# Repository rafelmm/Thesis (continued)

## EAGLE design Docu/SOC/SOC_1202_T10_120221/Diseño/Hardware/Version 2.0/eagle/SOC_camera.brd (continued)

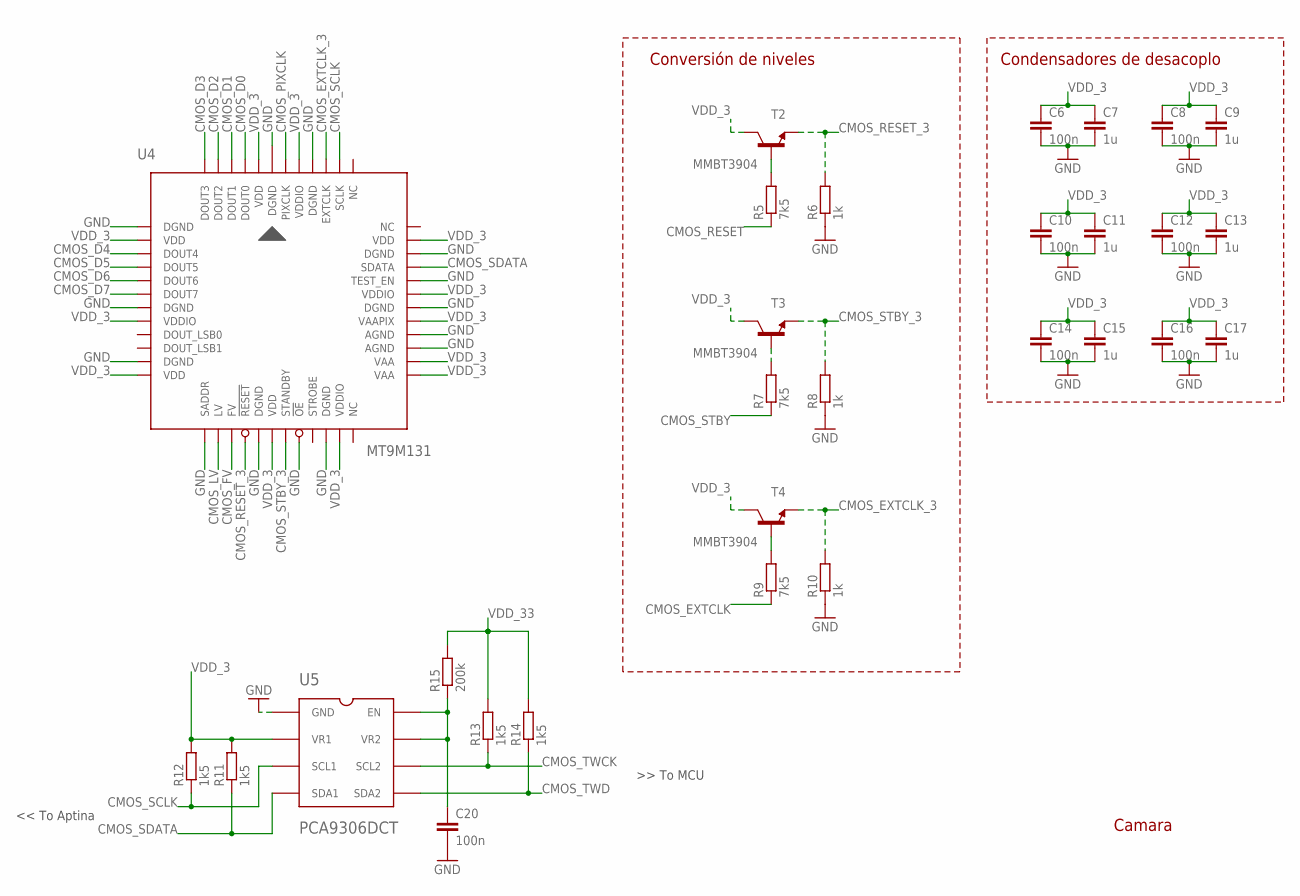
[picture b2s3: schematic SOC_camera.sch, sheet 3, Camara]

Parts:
C6, C8, C10, C12, C14, C16, C20: 100n; C0402
C7, C9, C11, C13, C15, C17: 1u; C0402
R5, R7, R9: 7k5; R0603
R6, R8, R10: 1k; R0603
R11, R12, R13, R14: 1k5; R0402
R15: 200k; R0402
T2, T3, T4: MMBT3904; SOT23-BEC
U4: MT9M131; APTINA
U5: PCA9306DCT; SSOP8; MPN PCA9306DCTR

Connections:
CMOS_D0: U4.3 (DOUT0); also elsewhere on the board
CMOS_D1: U4.4 (DOUT1); also elsewhere on the board
CMOS_D2: U4.5 (DOUT2); also elsewhere on the board
CMOS_D3: U4.6 (DOUT3); also elsewhere on the board
CMOS_D4: U4.9 (DOUT4); also elsewhere on the board
CMOS_D5: U4.10 (DOUT5); also elsewhere on the board
CMOS_D6: U4.11 (DOUT6); also elsewhere on the board
CMOS_D7: U4.12 (DOUT7); also elsewhere on the board
CMOS_EXTCLK: R9.1; also elsewhere on the board
CMOS_EXTCLK_3: R10.2, T4.E, U4.45 (EXTCLK)
CMOS_FV: U4.21 (FV); also elsewhere on the board
CMOS_LV: U4.20 (LV); also elsewhere on the board
CMOS_PIXCLK: U4.48 (PIXCLK); also elsewhere on the board
CMOS_RESET: R5.1; also elsewhere on the board
CMOS_RESET_3: R6.2, T2.E, U4.22 (!RESET)
CMOS_SCLK: R12.1, U4.44 (SCLK), U5.3 (SCL1)
CMOS_SDATA: R11.1, U4.39 (SDATA), U5.4 (SDA1)
CMOS_STBY: R7.1; also elsewhere on the board
CMOS_STBY_3: R8.2, T3.E, U4.25 (STANDBY)
CMOS_TWCK: R13.1, U5.6 (SCL2); also elsewhere on the board
CMOS_TWD: R14.1, U5.5 (SDA2); also elsewhere on the board
GND: C6.2, C7.2, C8.2, C9.2, C10.2, C11.2, C12.2, C13.2, C14.2, C15.2, C16.2, C17.2, C20.2, R6.1, R8.1, R10.1, U4.1 (DGND), U4.7 (DGND), U4.13 (DGND), U4.17 (DGND), U4.19 (SADDR), U4.23 (DGND), U4.26 (!OE), U4.28 (DGND), U4.33 (AGND), U4.34 (AGND), U4.36 (DGND), U4.38 (TEST_EN), U4.40 (DGND), U4.46 (DGND), U5.1 (GND); also elsewhere on the board
unnamed: R7.2, T3.B
unnamed: R9.2, T4.B
unnamed: R5.2, T2.B
unnamed: C20.1, R15.1, U5.7 (VR2), U5.8 (EN)
VDD_3: C6.1, C7.1, C8.1, C9.1, C10.1, C11.1, C12.1, C13.1, C14.1, C15.1, C16.1, C17.1, R11.2, R12.2, T2.C, T3.C, T4.C, U4.2 (VDD), U4.8 (VDD), U4.14 (VDDIO), U4.18 (VDD), U4.24 (VDD), U4.29 (VDDIO), U4.31 (VAA), U4.32 (VAA), U4.35 (VAAPIX), U4.37 (VDDIO), U4.41 (VDD), U4.47 (VDDIO), U5.2 (VR1); also elsewhere on the board
VDD_33: R13.2, R14.2, R15.2; also elsewhere on the board

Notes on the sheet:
Camara
Condensadores de desacoplo
Conversión de niveles
<< To Aptina

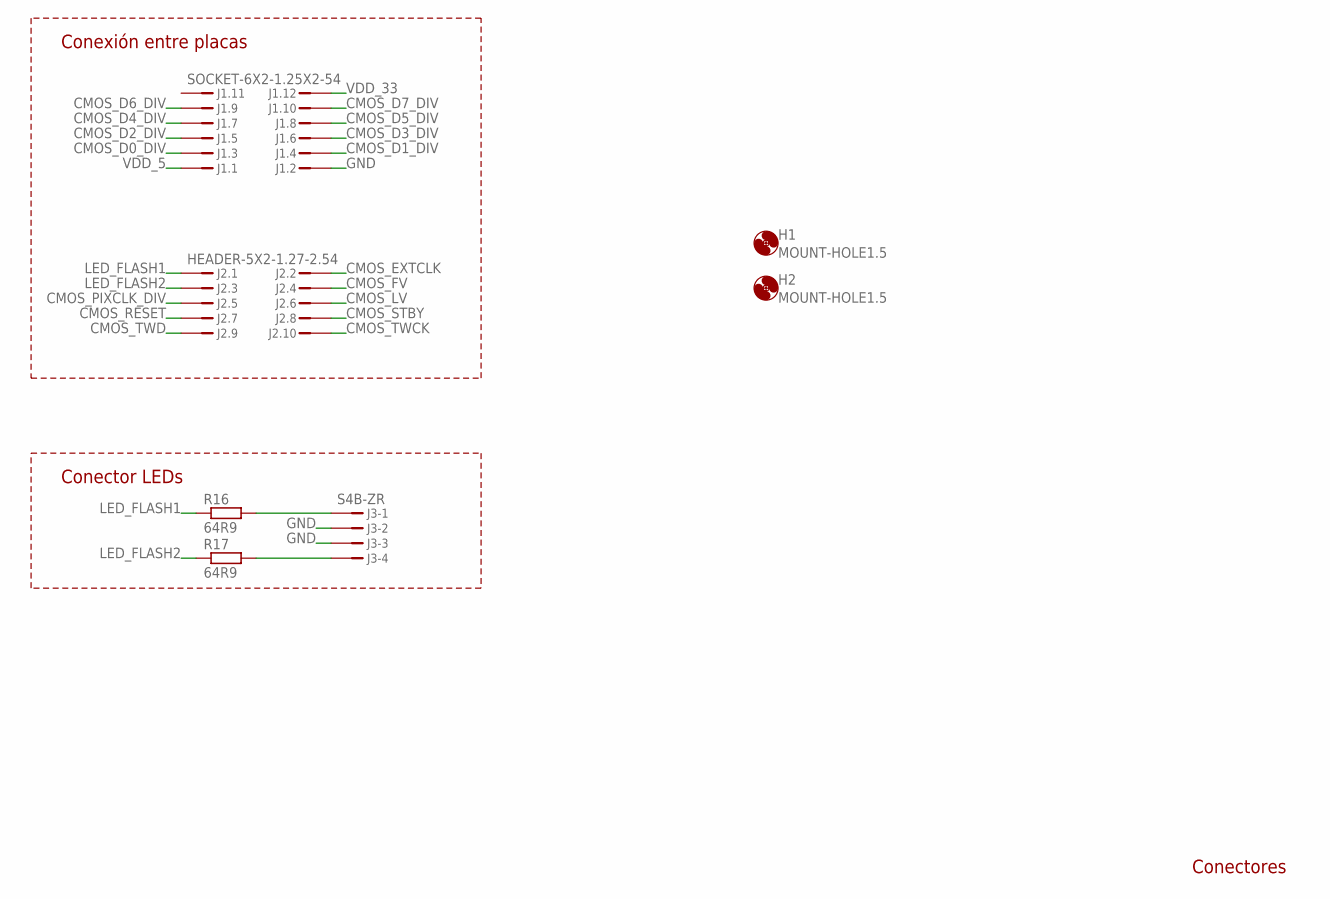
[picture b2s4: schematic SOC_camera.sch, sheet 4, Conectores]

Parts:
H1, H2: MOUNT-HOLE1.5; 1,5
J1: SOCKET-6X2-1.25X2-54; SOCKET-THD-6X2(1.27X2.54)
J2: HEADER-5X2-1.27-2.54; HEADER-THD-5X2(1.27X2.54)
J3: S4B-ZR
R16, R17: 64R9; R0603

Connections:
CMOS_D0_DIV: J1.P3; also elsewhere on the board
CMOS_D1_DIV: J1.P4; also elsewhere on the board
CMOS_D2_DIV: J1.P5; also elsewhere on the board
CMOS_D3_DIV: J1.P6; also elsewhere on the board
CMOS_D4_DIV: J1.P7; also elsewhere on the board
CMOS_D5_DIV: J1.P8; also elsewhere on the board
CMOS_D6_DIV: J1.P9; also elsewhere on the board
CMOS_D7_DIV: J1.P10; also elsewhere on the board
CMOS_EXTCLK: J2.2; also elsewhere on the board
CMOS_FV: J2.4; also elsewhere on the board
CMOS_LV: J2.6; also elsewhere on the board
CMOS_PIXCLK_DIV: J2.5; also elsewhere on the board
CMOS_RESET: J2.7; also elsewhere on the board
CMOS_STBY: J2.8; also elsewhere on the board
CMOS_TWCK: J2.10; also elsewhere on the board
CMOS_TWD: J2.9; also elsewhere on the board
GND: J1.P2, J3.2, J3.3; also elsewhere on the board
LED_FLASH1: J2.1, R16.1
LED_FLASH2: J2.3, R17.1
unnamed: J3.4, R17.2
unnamed: J3.1, R16.2
VDD_5: J1.P1; also elsewhere on the board
VDD_33: J1.P12; also elsewhere on the board

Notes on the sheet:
Conectores
Conexión entre placas
Conector LEDs

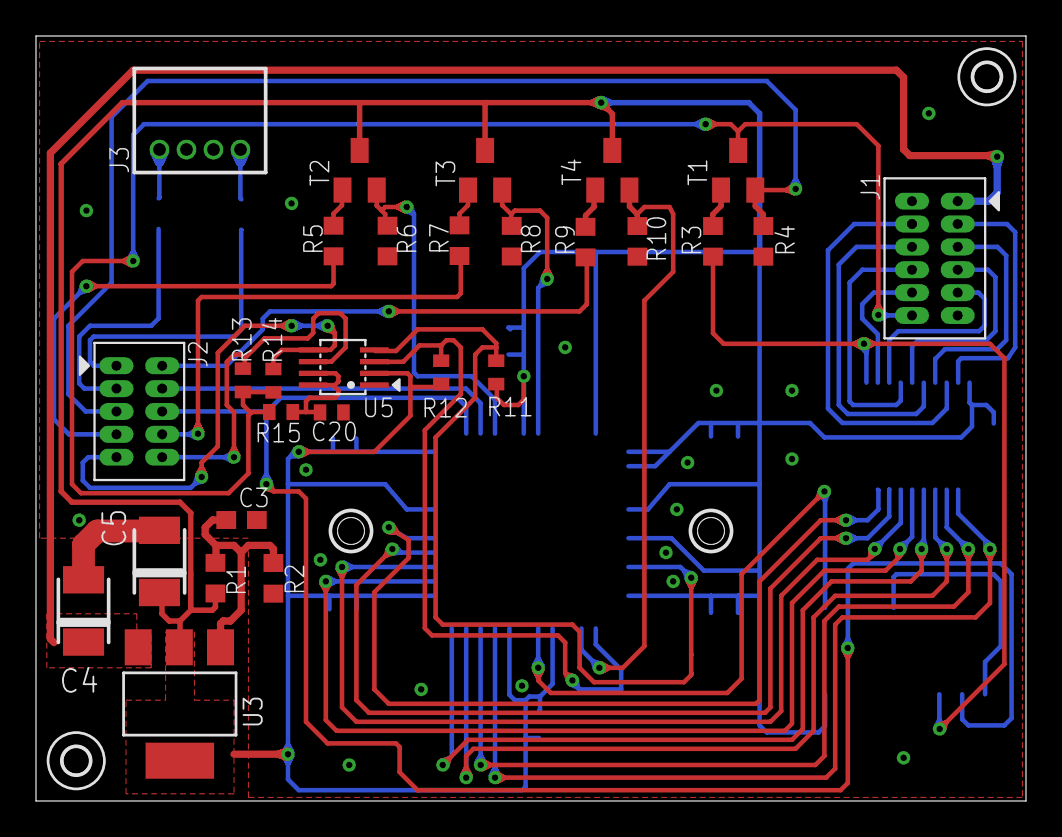
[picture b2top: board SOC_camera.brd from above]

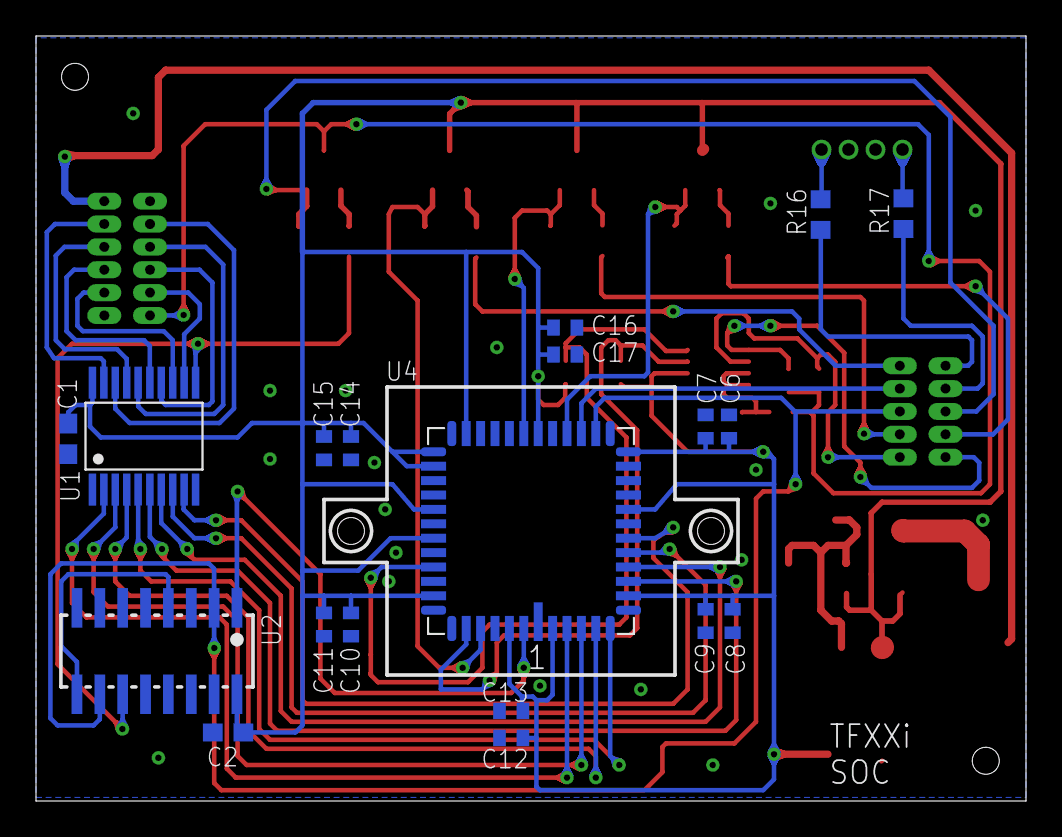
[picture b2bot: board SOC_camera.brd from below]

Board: 2 copper layers, 55.0 x 42.5 mm, 49 parts (19 on the bottom side), 46 nets.

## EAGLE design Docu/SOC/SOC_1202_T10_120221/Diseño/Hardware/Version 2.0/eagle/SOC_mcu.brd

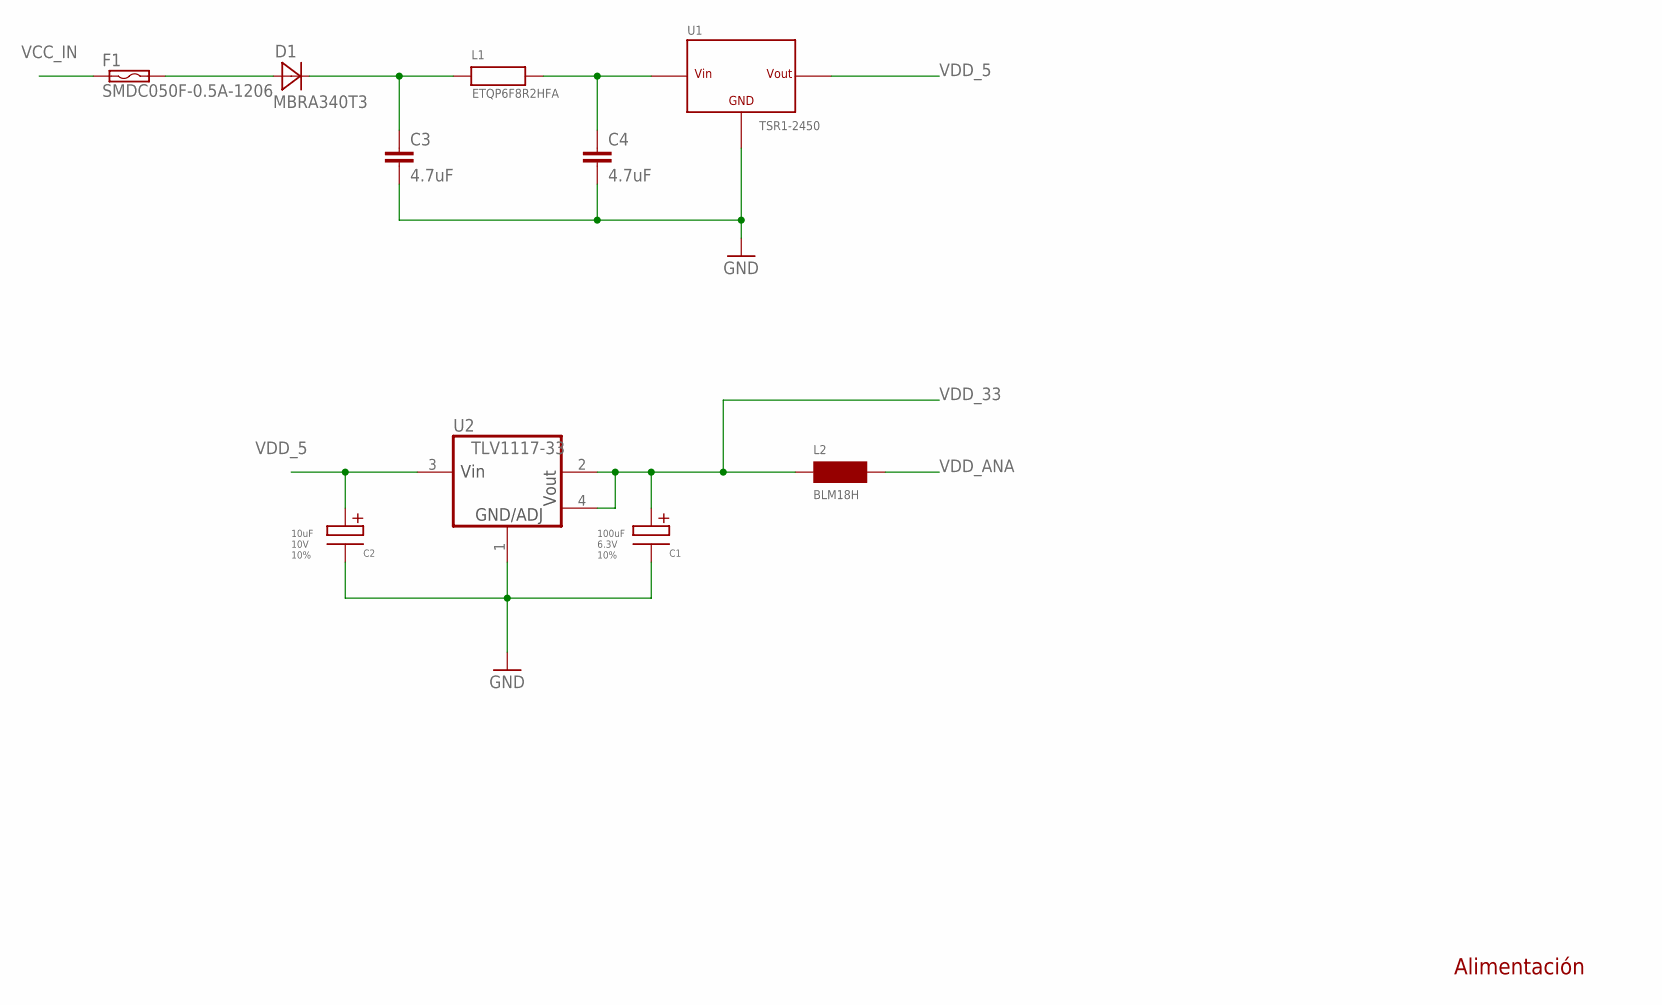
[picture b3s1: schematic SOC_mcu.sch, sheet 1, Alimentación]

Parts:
C1: 100uF; 3528-21
C2: 10uF; 3528-21
C3, C4: 4.7uF; C0805
D1: MBRA340T3; SMA
F1: SMDC050F-0.5A-1206; 1206
L1: ETQP6F8R2HFA; PAN_COIL_CHOKE
L2: BLM18H; 0603
U1: TSR1-2450; TO220V
U2: TLV1117-33; SOT223; MPN TLV1117-CDCY

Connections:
GND: C1.NEG, C2.NEG, C3.2, C4.2, U1.2 (GND), U2.1 (GND); also elsewhere on the board
unnamed: C4.1, L1.2, U1.1 (+VIN)
unnamed: C3.1, D1.C, L1.1
unnamed: D1.A, F1.2
VCC_IN: F1.1; also elsewhere on the board
VDD_5: C2.POS, U1.3 (VOUT), U2.3 (VIN); also elsewhere on the board
VDD_33: C1.POS, L2.1, U2.2 (VOUT), U2.4 (VO2); also elsewhere on the board
VDD_ANA: L2.2; also elsewhere on the board

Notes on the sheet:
Alimentación

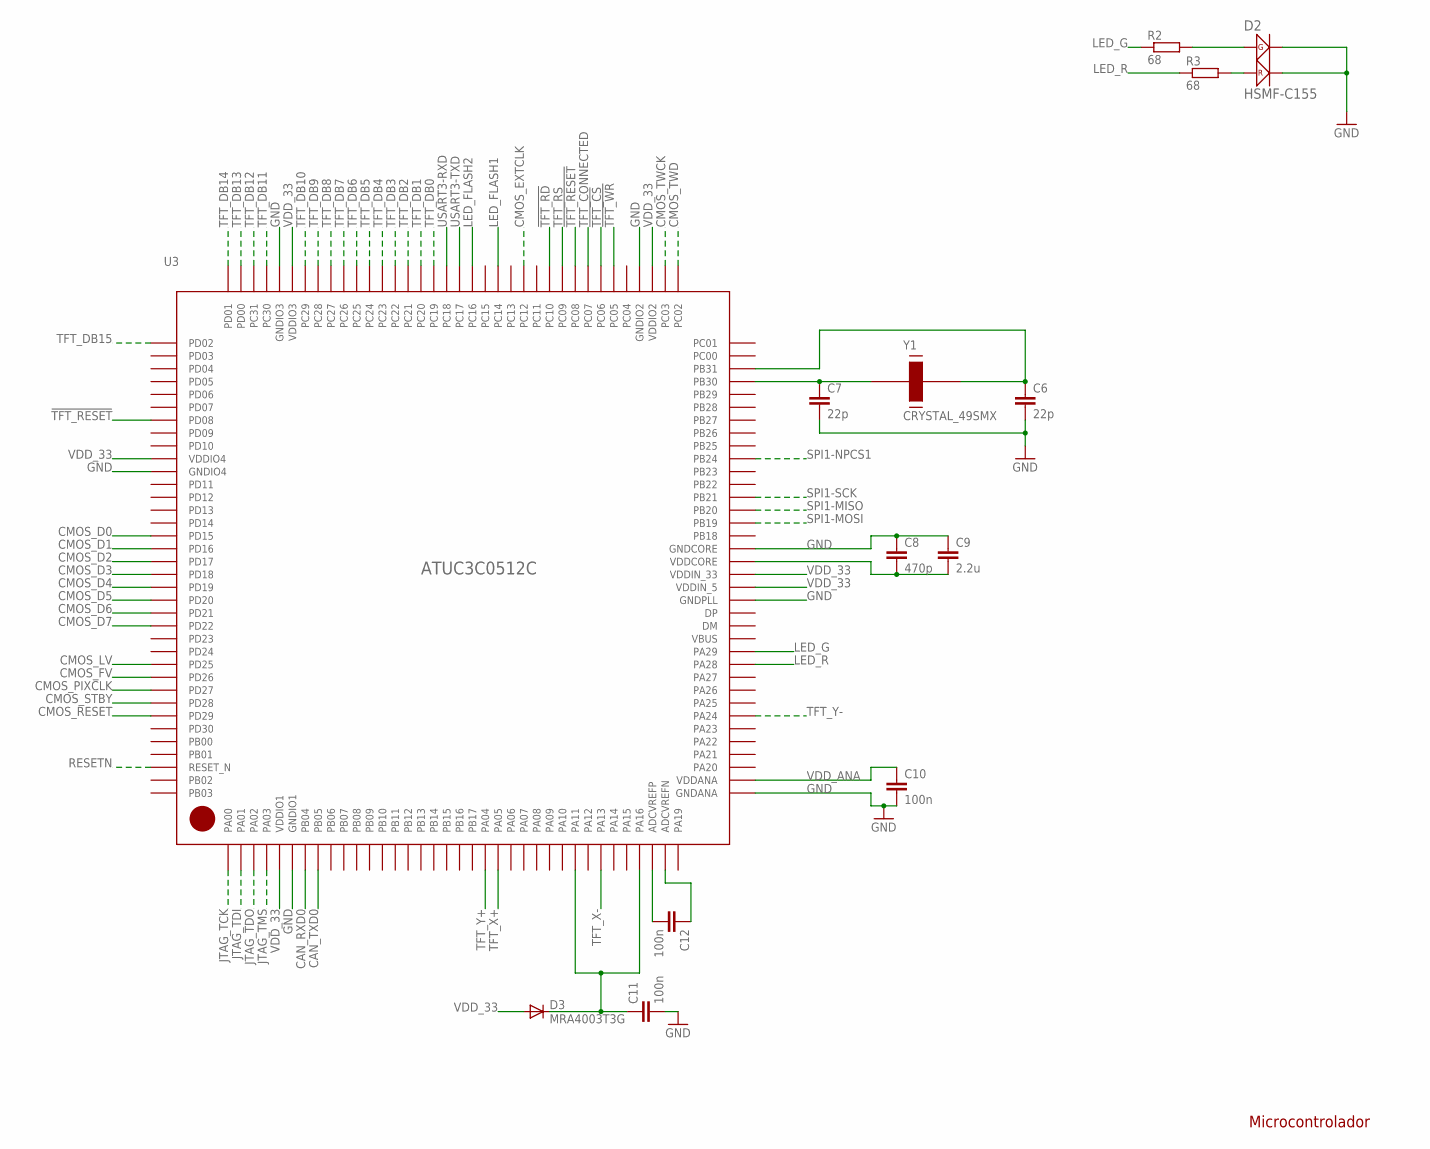
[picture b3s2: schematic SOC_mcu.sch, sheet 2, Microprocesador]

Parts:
C6, C7: 22p; C0603
C8: 470p; C0603
C9: 2.2u; C0603
C10, C11, C12: 100n; C0603
D2: HSMF-C155; HSMF-C
D3: MRA4003T3G; DO214AC
R2, R3: 68; R0603
U3: ATUC3C0512C; TQFP144
Y1: CRYSTAL_49SMX; HC49UP

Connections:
!TFT_CS: U3.79 (PC06); also elsewhere on the board
!TFT_RD: U3.83 (PC10); also elsewhere on the board
!TFT_RESET: U3.81 (PC08), U3.115 (PD08); also elsewhere on the board
!TFT_WR: U3.78 (PC05); also elsewhere on the board
CAN_RXD0: U3.7 (PB04); also elsewhere on the board
CAN_TXD0: U3.8 (PB05); also elsewhere on the board
CMOS_D0: U3.124 (PD15); also elsewhere on the board
CMOS_D1: U3.125 (PD16); also elsewhere on the board
CMOS_D2: U3.126 (PD17); also elsewhere on the board
CMOS_D3: U3.127 (PD18); also elsewhere on the board
CMOS_D4: U3.128 (PD19); also elsewhere on the board
CMOS_D5: U3.129 (PD20); also elsewhere on the board
CMOS_D6: U3.130 (PD21); also elsewhere on the board
CMOS_D7: U3.131 (PD22); also elsewhere on the board
CMOS_EXTCLK: U3.85 (PC12); also elsewhere on the board
CMOS_FV: U3.135 (PD26); also elsewhere on the board
CMOS_LV: U3.134 (PD25); also elsewhere on the board
CMOS_PIXCLK: U3.136 (PD27); also elsewhere on the board
CMOS_RESET: U3.138 (PD29); also elsewhere on the board
CMOS_STBY: U3.137 (PD28); also elsewhere on the board
CMOS_TWCK: U3.74 (PC03); also elsewhere on the board
CMOS_TWD: U3.73 (PC02); also elsewhere on the board
GND: C6.2, C7.2, C8.1, C9.1, C10.2, C11.2, D2.2, D2.4, U3.6 (GNDIO1), U3.37 (GNDANA), U3.52 (GNDPLL), U3.56 (GNDCORE), U3.76 (GNDIO2), U3.104 (GNDIO3), U3.119 (GNDIO4); also elsewhere on the board
JTAG_TCK: U3.1 (PA00); also elsewhere on the board
JTAG_TDI: U3.2 (PA01); also elsewhere on the board
JTAG_TDO: U3.3 (PA02); also elsewhere on the board
JTAG_TMS: U3.4 (PA03); also elsewhere on the board
LED_FLASH1: U3.87 (PC14); also elsewhere on the board
LED_FLASH2: U3.89 (PC16); also elsewhere on the board
LED_G: R2.1, U3.48 (PA29)
LED_R: R3.1, U3.47 (PA28)
unnamed: C6.1, U3.70 (PB31), Y1.2
unnamed: C7.1, U3.69 (PB30), Y1.1
unnamed: C8.2, C9.2, U3.55 (VDDCORE)
unnamed: D2.1, R2.2
unnamed: D2.3, R3.2
unnamed: C11.1, D3.C, U3.28 (PA11), U3.33 (PA16)
unnamed: C12.2, U3.34 (ADCVREFP)
unnamed: C12.1, U3.35 (ADCVREFN)
RESETN: U3.142 (RESET_N); also elsewhere on the board
SPI1-MISO: U3.59 (PB20); also elsewhere on the board
SPI1-MOSI: U3.58 (PB19); also elsewhere on the board
SPI1-NPCS1: U3.63 (PB24); also elsewhere on the board
SPI1-SCK: U3.60 (PB21); also elsewhere on the board
TFT_CONNECTED: U3.80 (PC07); also elsewhere on the board
TFT_DB0: U3.92 (PC19); also elsewhere on the board
TFT_DB1: U3.93 (PC20); also elsewhere on the board
TFT_DB2: U3.94 (PC21); also elsewhere on the board
TFT_DB3: U3.95 (PC22); also elsewhere on the board
TFT_DB4: U3.96 (PC23); also elsewhere on the board
TFT_DB5: U3.97 (PC24); also elsewhere on the board
TFT_DB6: U3.98 (PC25); also elsewhere on the board
TFT_DB7: U3.99 (PC26); also elsewhere on the board
TFT_DB8: U3.100 (PC27); also elsewhere on the board
TFT_DB9: U3.101 (PC28); also elsewhere on the board
TFT_DB10: U3.102 (PC29); also elsewhere on the board
TFT_DB11: U3.105 (PC30); also elsewhere on the board
TFT_DB12: U3.106 (PC31); also elsewhere on the board
TFT_DB13: U3.107 (PD00); also elsewhere on the board
TFT_DB14: U3.108 (PD01); also elsewhere on the board
TFT_DB15: U3.109 (PD02); also elsewhere on the board
TFT_RS: U3.82 (PC09); also elsewhere on the board
TFT_X+: U3.22 (PA05); also elsewhere on the board
TFT_X-: U3.30 (PA13); also elsewhere on the board
TFT_Y+: U3.21 (PA04); also elsewhere on the board
TFT_Y-: U3.43 (PA24); also elsewhere on the board
USART3-RXD: U3.91 (PC18); also elsewhere on the board
USART3-TXD: U3.90 (PC17); also elsewhere on the board
VDD_33: D3.A, U3.5 (VDDIO1), U3.53 (VDDIN_5), U3.54 (VDDIN_33), U3.75 (VDDIO2), U3.103 (VDDIO3), U3.118 (VDDIO4); also elsewhere on the board
VDD_ANA: C10.1, U3.38 (VDDANA); also elsewhere on the board

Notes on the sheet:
Microcontrolador

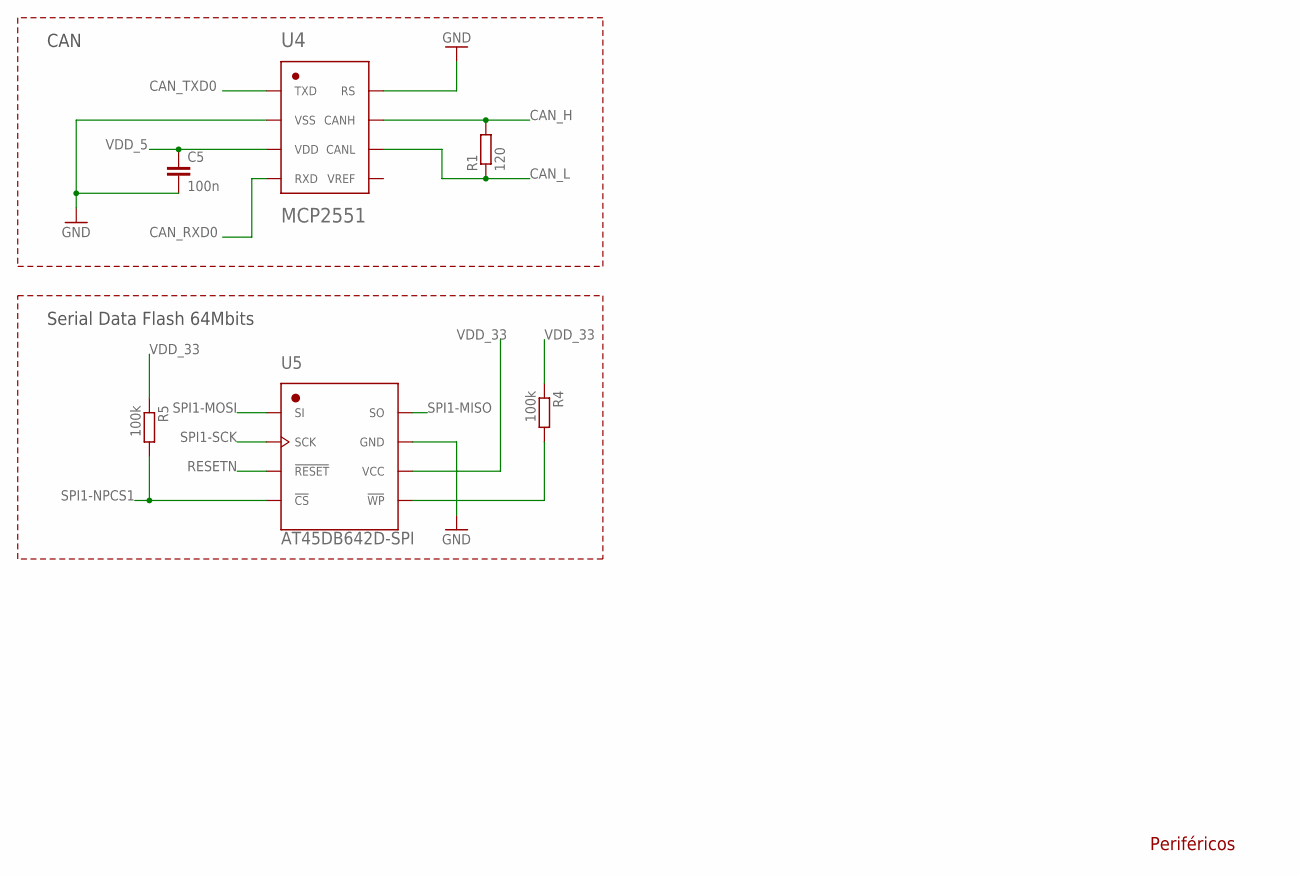
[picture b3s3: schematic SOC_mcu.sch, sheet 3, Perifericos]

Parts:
C5: 100n; C0603
R1: 120; R0805
R4, R5: 100k; R0603
U4: MCP2551; SO08
U5: AT45DB642D-SPI; 8CN3

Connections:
CAN_H: R1.2, U4.7 (CANH); also elsewhere on the board
CAN_L: R1.1, U4.6 (CANL); also elsewhere on the board
CAN_RXD0: U4.4 (RXD); also elsewhere on the board
CAN_TXD0: U4.1 (TXD); also elsewhere on the board
GND: C5.2, U4.2 (VSS), U4.8 (RS), U5.7 (GND); also elsewhere on the board
unnamed: R4.2, U5.5 (!WP)
RESETN: U5.3 (!RESET); also elsewhere on the board
SPI1-MISO: U5.8 (SO); also elsewhere on the board
SPI1-MOSI: U5.1 (SI); also elsewhere on the board
SPI1-NPCS1: R5.2, U5.4 (!CS); also elsewhere on the board
SPI1-SCK: U5.2 (SCK); also elsewhere on the board
VDD_5: C5.1, U4.3 (VDD); also elsewhere on the board
VDD_33: R4.1, R5.1, U5.6 (VCC); also elsewhere on the board

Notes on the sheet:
CAN
Serial Data Flash 64Mbits
Periféricos

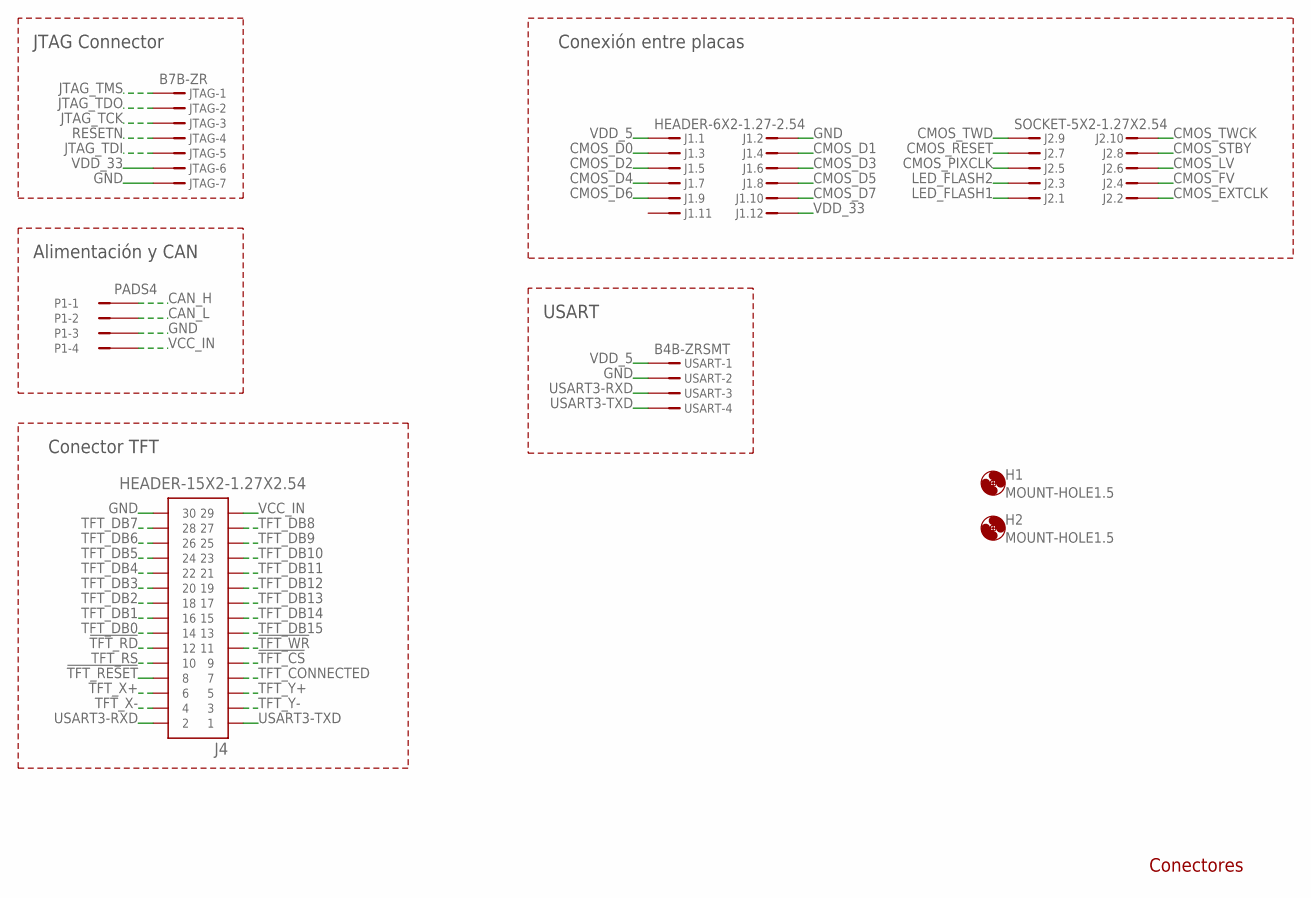
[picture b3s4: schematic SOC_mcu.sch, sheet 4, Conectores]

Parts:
H1, H2: MOUNT-HOLE1.5; 1,5
J1: HEADER-6X2-1.27-2.54; HEADER-THD-6X2(1.27X2.54)
J2: SOCKET-5X2-1.27X2.54; SOCKET-THD-5X2(1.27X2.54)
J4: HEADER-15X2-1.27X2.54; HEADER-THD-15X2(1.27X2.54)
JTAG: B7B-ZR
P1: PADS4; CAN+POWER
USART: B4B-ZRSMT; SM4-TF

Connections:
!TFT_CS: J4.9; also elsewhere on the board
!TFT_RD: J4.12; also elsewhere on the board
!TFT_RESET: J4.8; also elsewhere on the board
!TFT_WR: J4.11; also elsewhere on the board
CAN_H: P1.1; also elsewhere on the board
CAN_L: P1.2; also elsewhere on the board
CMOS_D0: J1.3; also elsewhere on the board
CMOS_D1: J1.4; also elsewhere on the board
CMOS_D2: J1.5; also elsewhere on the board
CMOS_D3: J1.6; also elsewhere on the board
CMOS_D4: J1.7; also elsewhere on the board
CMOS_D5: J1.8; also elsewhere on the board
CMOS_D6: J1.9; also elsewhere on the board
CMOS_D7: J1.10; also elsewhere on the board
CMOS_EXTCLK: J2.P2; also elsewhere on the board
CMOS_FV: J2.P4; also elsewhere on the board
CMOS_LV: J2.P6; also elsewhere on the board
CMOS_PIXCLK: J2.P5; also elsewhere on the board
CMOS_RESET: J2.P7; also elsewhere on the board
CMOS_STBY: J2.P8; also elsewhere on the board
CMOS_TWCK: J2.P10; also elsewhere on the board
CMOS_TWD: J2.P9; also elsewhere on the board
GND: J1.2, J4.30, JTAG.7, P1.3, USART.2; also elsewhere on the board
JTAG_TCK: JTAG.3; also elsewhere on the board
JTAG_TDI: JTAG.5; also elsewhere on the board
JTAG_TDO: JTAG.2; also elsewhere on the board
JTAG_TMS: JTAG.1; also elsewhere on the board
LED_FLASH1: J2.P1; also elsewhere on the board
LED_FLASH2: J2.P3; also elsewhere on the board
RESETN: JTAG.4; also elsewhere on the board
TFT_CONNECTED: J4.7; also elsewhere on the board
TFT_DB0: J4.14; also elsewhere on the board
TFT_DB1: J4.16; also elsewhere on the board
TFT_DB2: J4.18; also elsewhere on the board
TFT_DB3: J4.20; also elsewhere on the board
TFT_DB4: J4.22; also elsewhere on the board
TFT_DB5: J4.24; also elsewhere on the board
TFT_DB6: J4.26; also elsewhere on the board
TFT_DB7: J4.28; also elsewhere on the board
TFT_DB8: J4.27; also elsewhere on the board
TFT_DB9: J4.25; also elsewhere on the board
TFT_DB10: J4.23; also elsewhere on the board
TFT_DB11: J4.21; also elsewhere on the board
TFT_DB12: J4.19; also elsewhere on the board
TFT_DB13: J4.17; also elsewhere on the board
TFT_DB14: J4.15; also elsewhere on the board
TFT_DB15: J4.13; also elsewhere on the board
TFT_RS: J4.10; also elsewhere on the board
TFT_X+: J4.6; also elsewhere on the board
TFT_X-: J4.4; also elsewhere on the board
TFT_Y+: J4.5; also elsewhere on the board
TFT_Y-: J4.3; also elsewhere on the board
USART3-RXD: J4.2, USART.3; also elsewhere on the board
USART3-TXD: J4.1, USART.4; also elsewhere on the board
VCC_IN: J4.29, P1.4; also elsewhere on the board
VDD_5: J1.1, USART.1; also elsewhere on the board
VDD_33: J1.12, JTAG.6; also elsewhere on the board

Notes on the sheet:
JTAG Connector
Conectores
Alimentación y CAN
Conexión entre placas
Conector TFT
USART

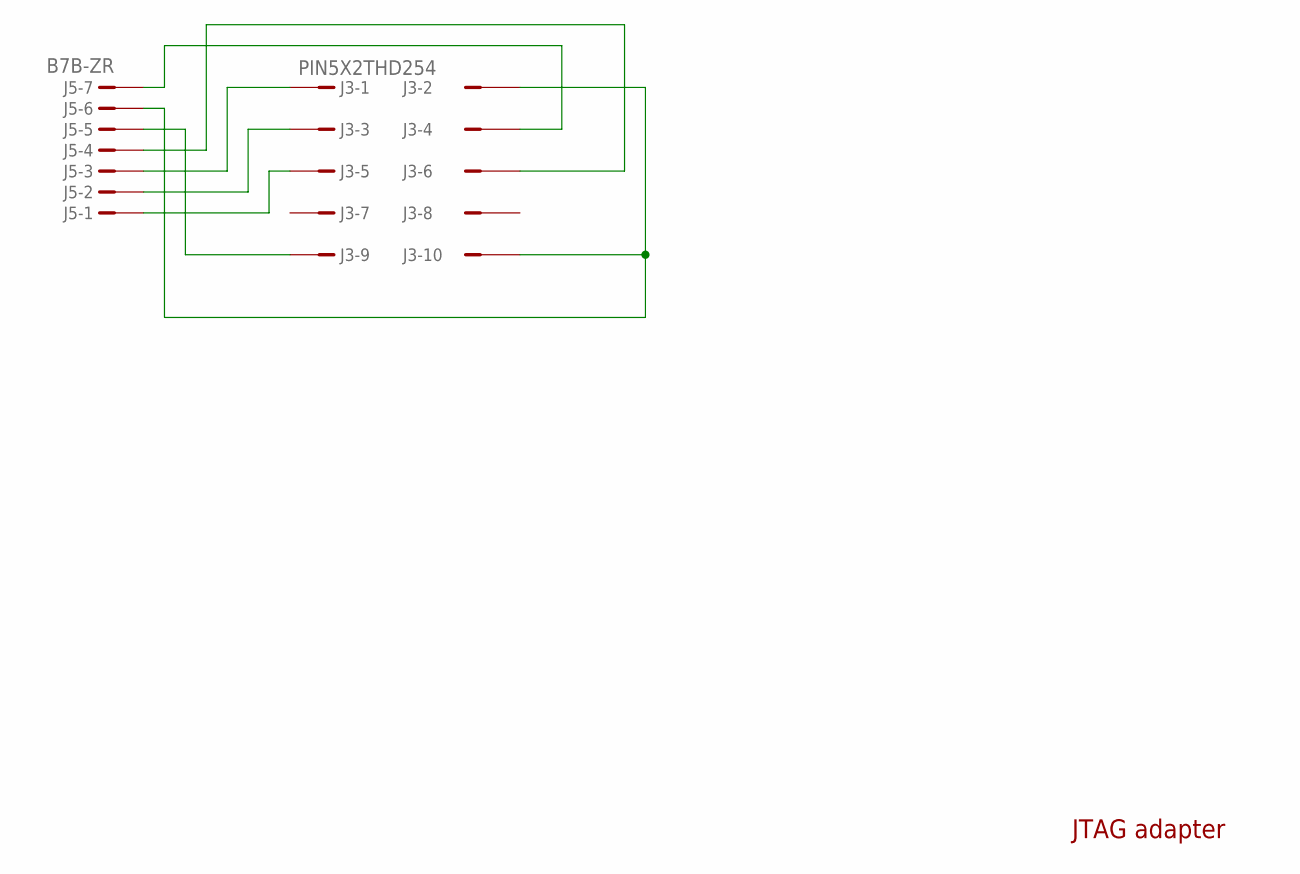
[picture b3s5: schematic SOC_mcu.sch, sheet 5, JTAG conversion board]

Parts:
J3: PIN5X2THD254; 5X2THD254
J5: B7B-ZR

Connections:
unnamed: J3.5, J5.1
unnamed: J3.3, J5.2
unnamed: J3.1, J5.3
unnamed: J3.6, J5.4
unnamed: J3.9, J5.5
unnamed: J3.2, J3.10, J5.6
unnamed: J3.4, J5.7

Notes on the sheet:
JTAG adapter

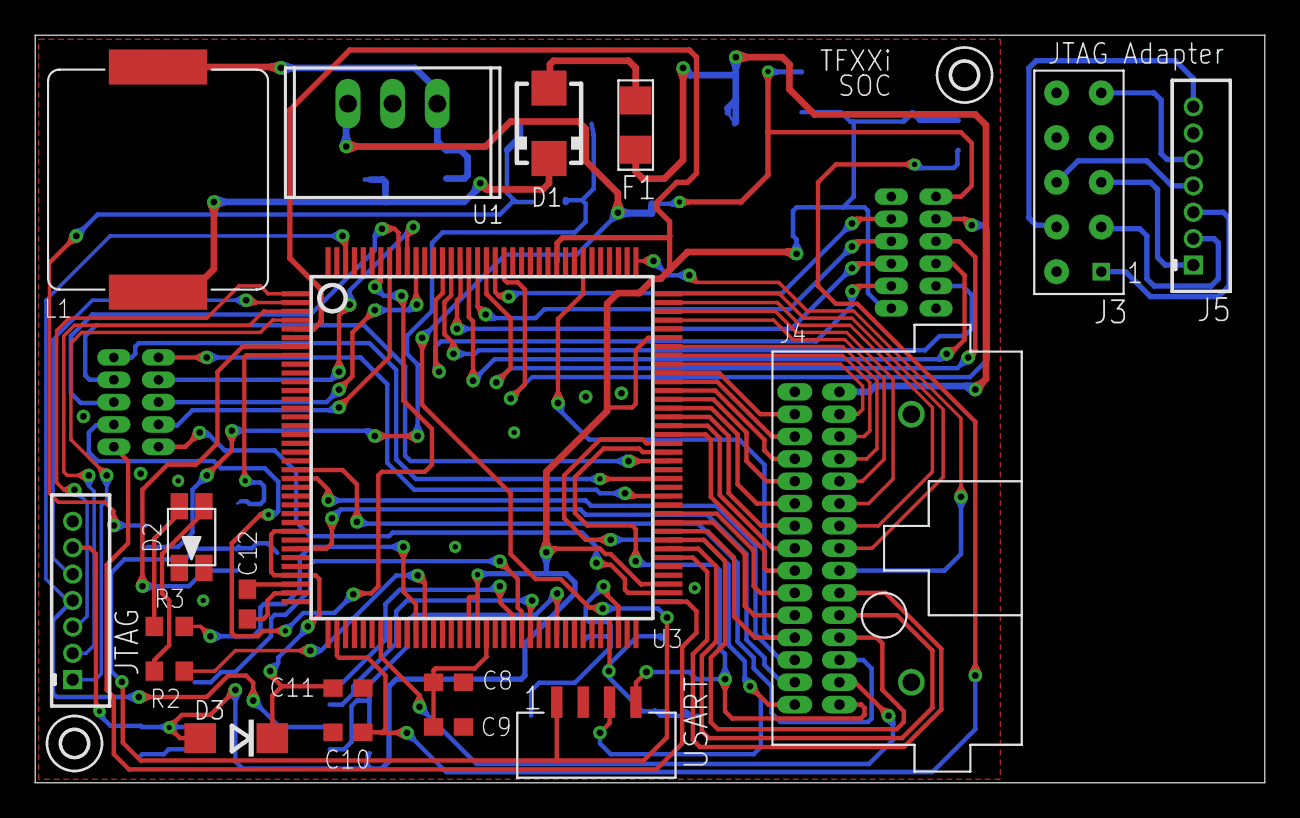
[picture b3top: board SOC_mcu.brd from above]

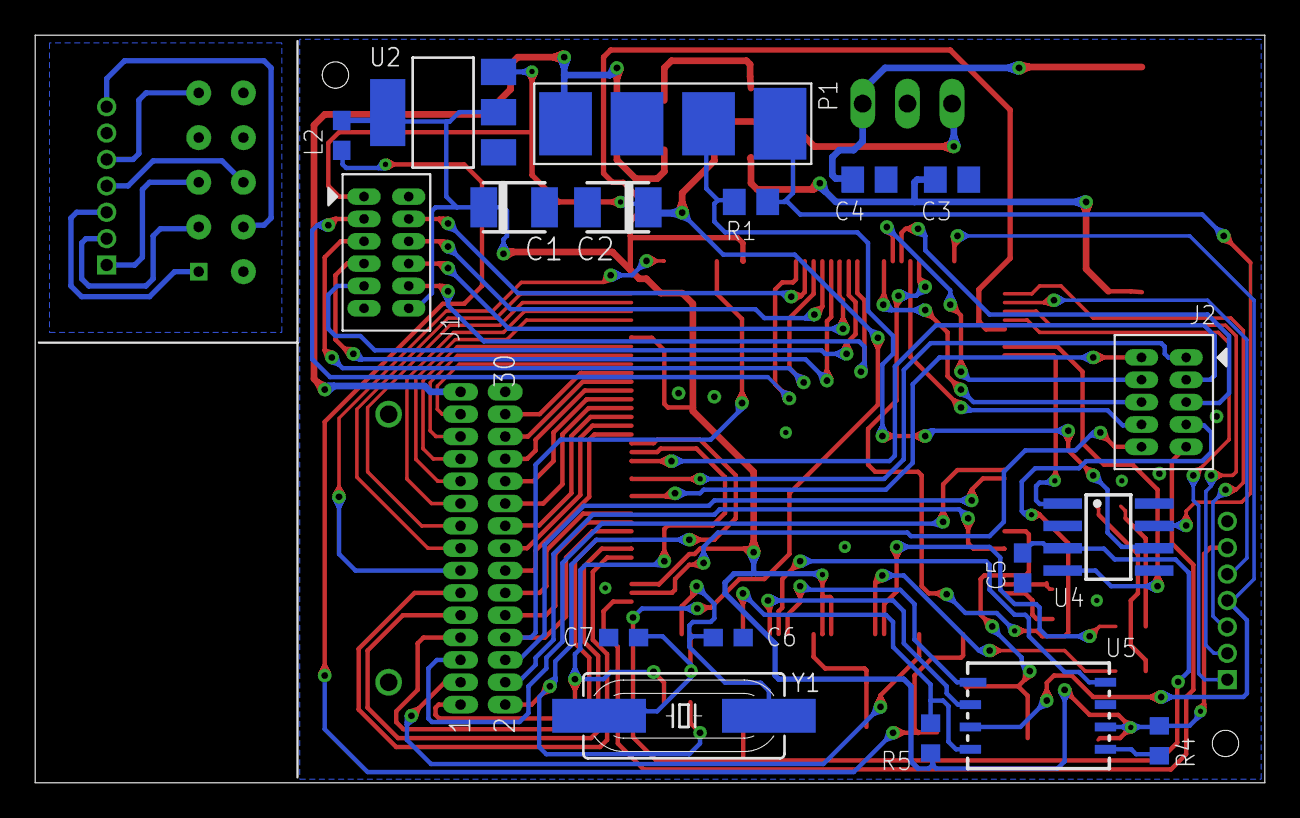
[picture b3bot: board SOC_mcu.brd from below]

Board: 2 copper layers, 69.9 x 42.5 mm, 39 parts (18 on the bottom side), 85 nets.

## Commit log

2015-03-23 Empiezo con el Prior Art
2015-03-23 Començo amb '2.2 embedded computer vision'
2015-03-24 Terminado '2.2 Embedded Systems'
2015-03-30 Empiezo con el diseño
2015-03-30 Ampliado 'Field of application'
2015-04-13 Añadida docu SOC y diseño electronica casi acabado
2015-04-13 eliminado .exe
2015-04-22 Empiezo el algoritmo
2015-04-25 Acabada binarizacion y empezado SENDA
2015-05-13 'Arquitectura'
2015-05-16 Fundamentals. Mathematical Morphology
2015-05-18 Connected components and firmware architecture
2015-05-21 PM Position Estimation
2015-05-22 Gap measurement
2015-05-25 Geometrical correction, installation program and web client integration
2015-05-28 Results
2015-05-29 Resultados
2015-06-01 Documento para revision
2015-06-14 Documento Corregido
